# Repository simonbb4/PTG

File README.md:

# PTG
Programmable Tone Generator Senior Design Project Texas State University

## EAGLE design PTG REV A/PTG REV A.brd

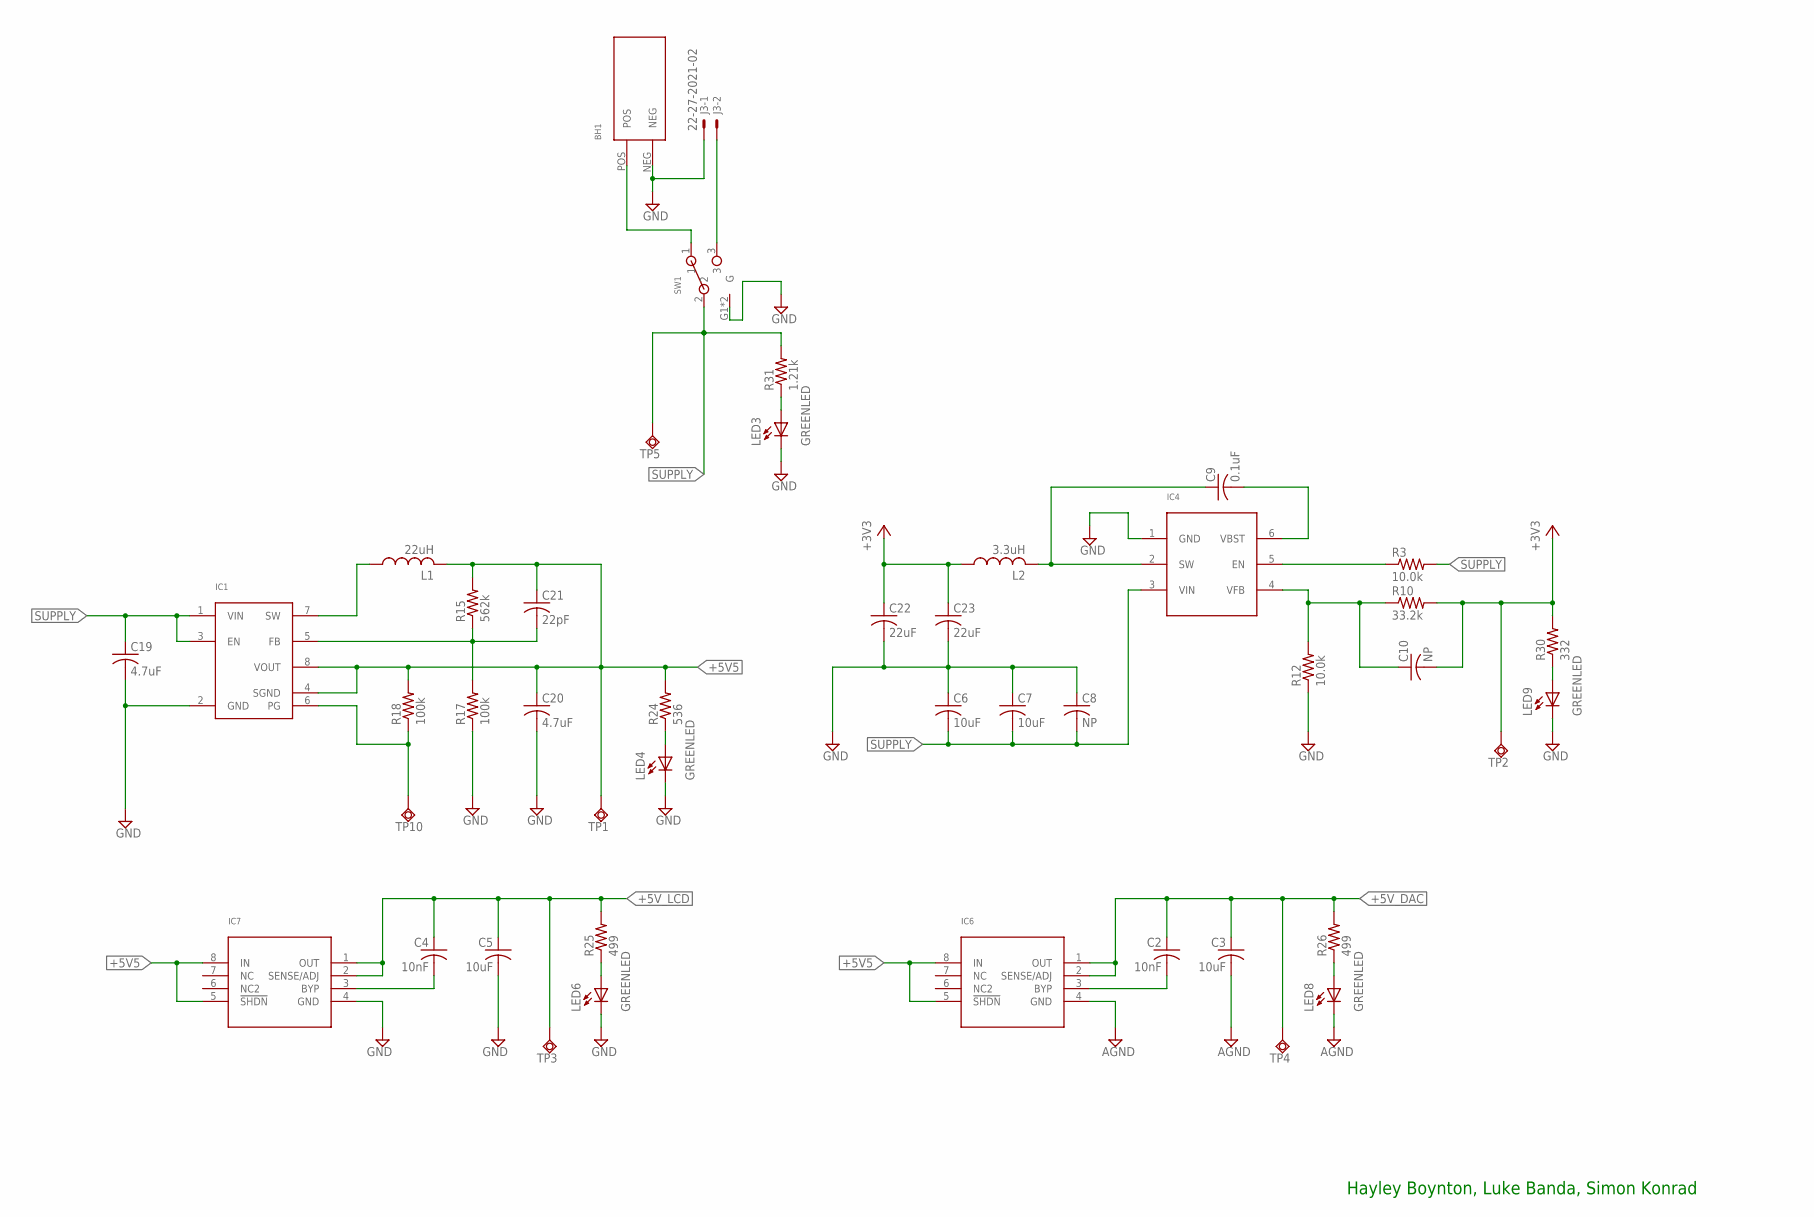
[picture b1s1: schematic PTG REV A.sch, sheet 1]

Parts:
BH1: BATTERY_HOLDER
C2, C4: 10nF; C0603K
C3, C5, C6, C7: 10uF; C0805K
C8: NP; C0805K
C9: 0.1uF; C0603K
C10: NP; C0603K
C19, C20: 4.7uF; C0805K
C21: 22pF; C0603K
C22, C23: 22uF; C0805K
IC1: TPS62120; SOT23(8)
IC4: TPS561208; SOT6
IC6, IC7: LT1762; MS8
J3: 22-27-2021-02; 6410-02
L1: 22uH; VLCF4020
L2: 3.3uH; VLCF4020
LED3, LED4, LED6, LED8, LED9: GREENLED; 0805_10MGAP
R3, R12: 10.0k; R0603
R10: 33.2k; R0603
R15: 562k; R0603
R17, R18: 100k; R0603
R24: 536; R0603
R25, R26: 499; R0603
R30: 332; R0603
R31: 1.21k; R0603
SW1: ROCKER_SWITCH
TP1, TP2, TP3, TP4, TP5, TP10: TPSQTP20SQD; TP20SQD

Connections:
+3V3: C10.2, C22.1, C23.1, L2.1, R10.2, R30.2, TP2.1, TP2.TP; also elsewhere on the board
+5V5: C20.1, C21.1, IC1.4 (SGND), IC1.8 (VOUT), IC6.5 (!SHDN), IC6.8 (IN), IC7.5 (!SHDN), IC7.8 (IN), L1.2, R15.2, R18.2, R24.2, TP1.1, TP1.TP
+5V_DAC: C2.1, C3.1, IC6.1 (OUT), IC6.2 (SENSE/ADJ), R26.2, TP4.1, TP4.TP; also elsewhere on the board
+5V_LCD: C4.1, C5.1, IC7.1 (OUT), IC7.2 (SENSE/ADJ), R25.2, TP3.1, TP3.TP; also elsewhere on the board
AGND: C3.2, IC6.4 (GND), LED8.1 (-); also elsewhere on the board
GND: BH1.NEG, C5.2, C6.1, C7.1, C8.1, C19.2, C20.2, C22.2, C23.2, IC1.2 (GND), IC4.1 (GND), IC7.4 (GND), J3.1, LED3.1 (-), LED4.1 (-), LED6.1 (-), LED9.1 (-), R12.1, R17.1, SW1.G1 (G), SW1.G2 (G); also elsewhere on the board
unnamed: C10.1, IC4.4 (VFB), R10.1, R12.2
unnamed: C9.1, IC4.2 (SW), L2.2
unnamed: C9.2, IC4.6 (VBST)
unnamed: IC4.5 (EN), R3.1
unnamed: IC1.7 (SW), L1.1
unnamed: C21.2, IC1.5 (FB), R15.1, R17.2
unnamed: C2.2, IC6.3 (BYP)
unnamed: LED3.2 (+), R31.1
unnamed: LED4.2 (+), R24.1
unnamed: C4.2, IC7.3 (BYP)
unnamed: LED6.2 (+), R25.1
unnamed: LED8.2 (+), R26.1
unnamed: LED9.2 (+), R30.1
unnamed: BH1.POS, SW1.1
unnamed: J3.2, SW1.3
PWRGOOD: IC1.6 (PG), R18.1, TP10.1, TP10.TP
SUPPLY: C6.2, C7.2, C8.2, C19.1, IC1.1 (VIN), IC1.3 (EN), IC4.3 (VIN), R3.2, R31.2, SW1.2, TP5.1, TP5.TP

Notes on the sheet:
Hayley Boynton, Luke Banda, Simon Konrad

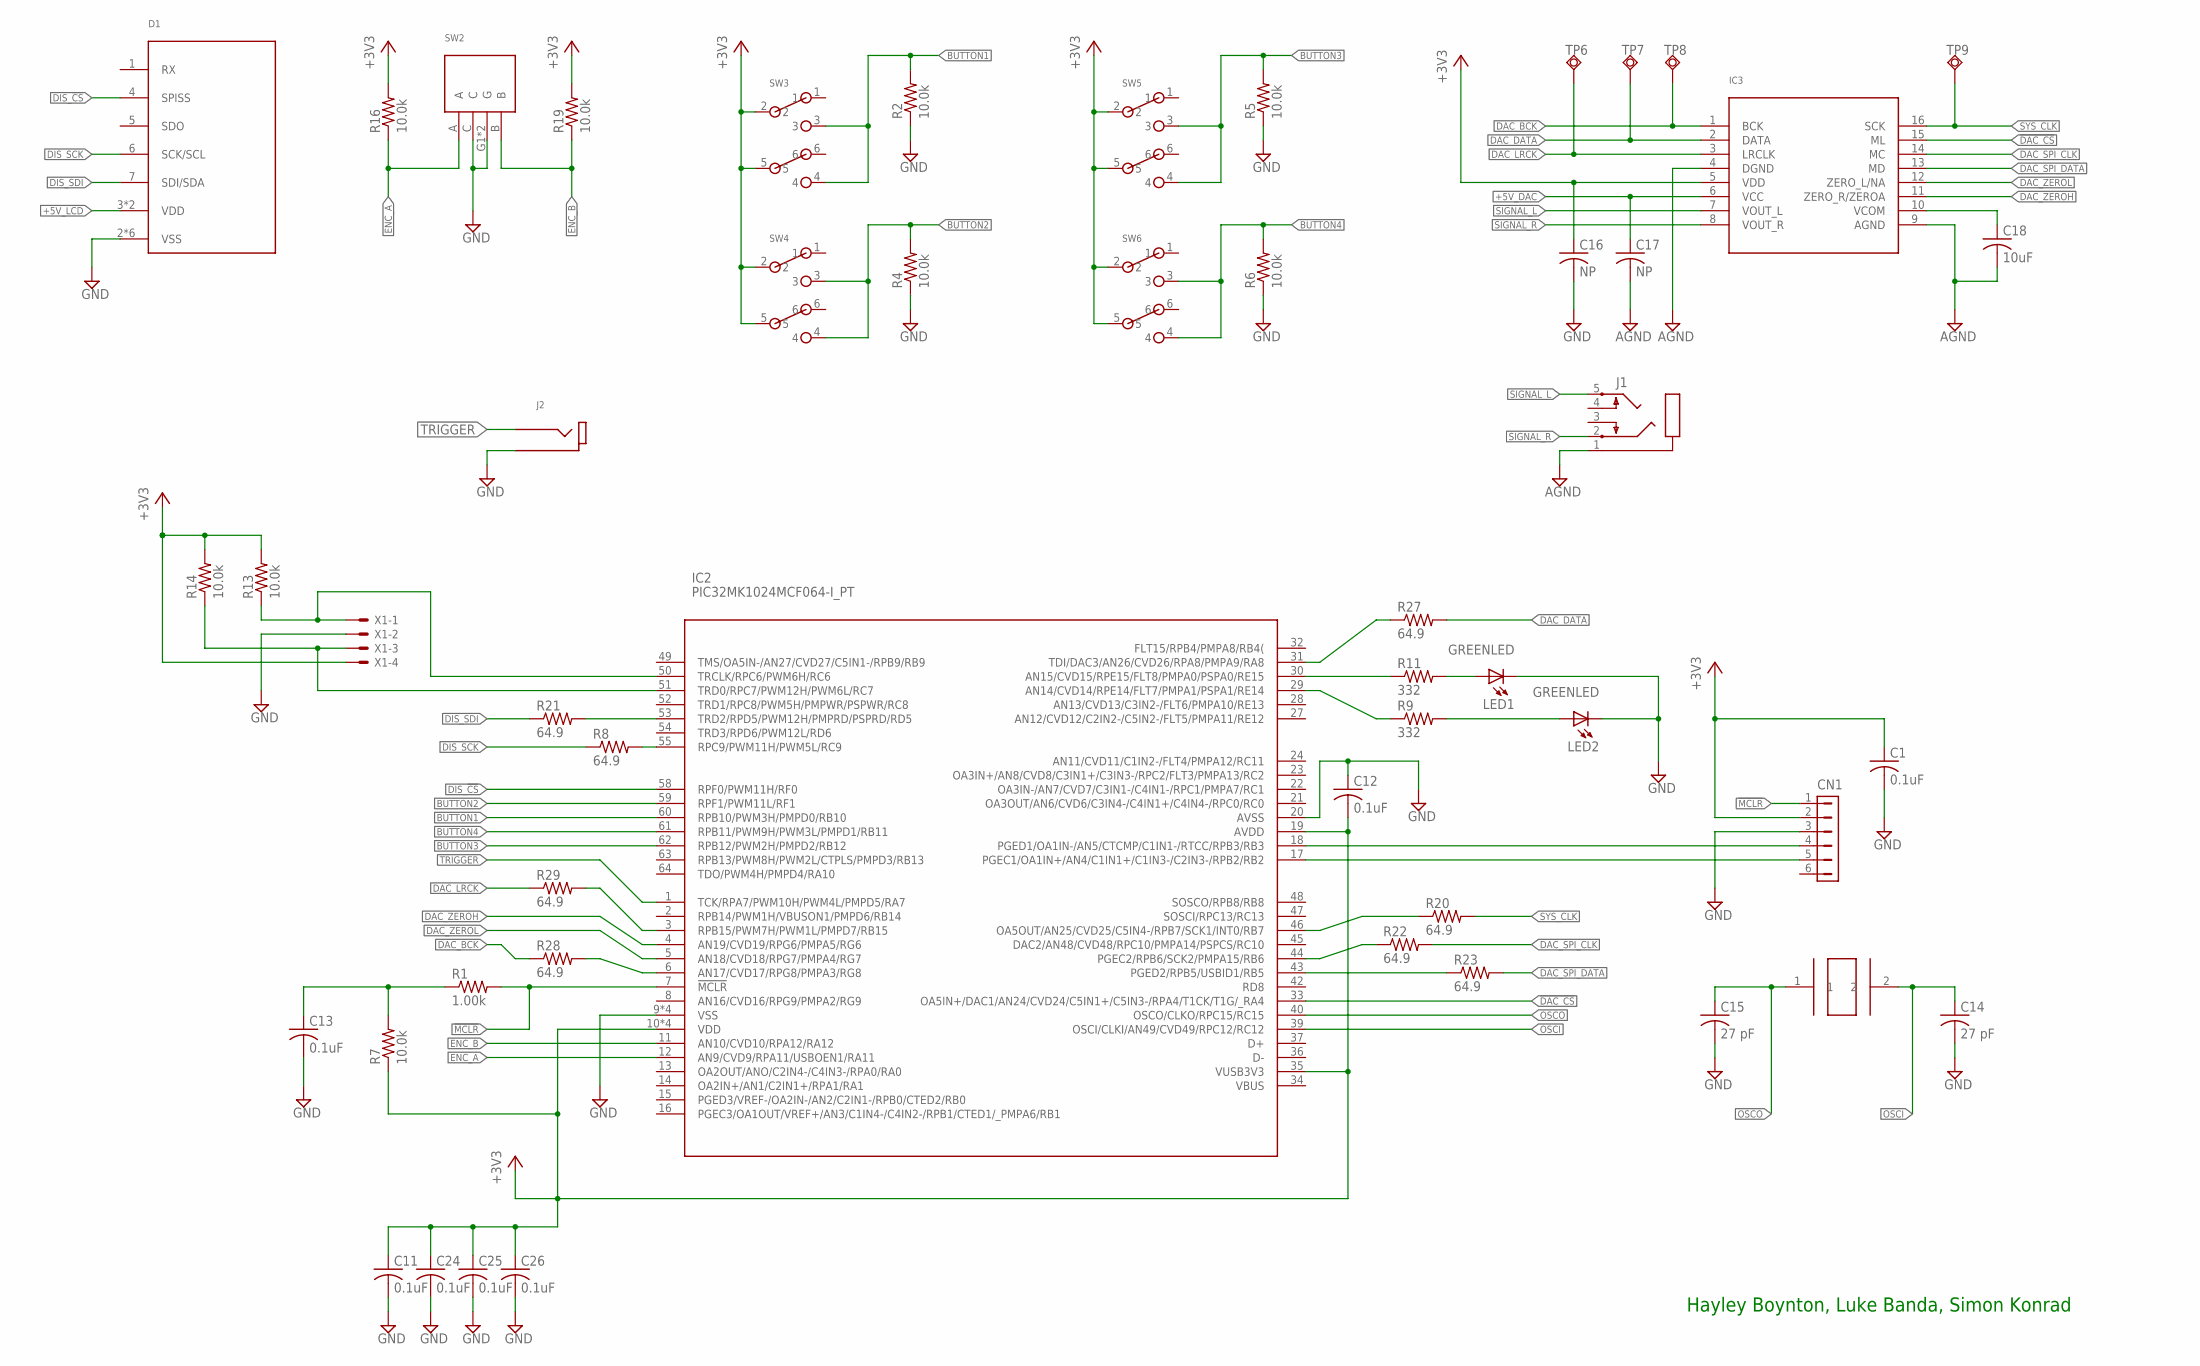
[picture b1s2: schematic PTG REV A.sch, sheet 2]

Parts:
C1, C11, C12, C13, C24, C25, C26: 0.1uF; C0603K
C14, C15: 27 pF; C0603K
C16, C17: NP; C0603K
C18: 10uF; C0805K
CN1: HDR-1X6-SIP-100; SIP-100-6V
D1: NHD-0216K3Z-GBW-V3; NHD-0216K3Z-FL-GBW-V3
IC2: PIC32MK1024MCF064-I_PT; TQFP64-10X10
IC3: PCM1748; SSOP
J1: STX31005NB
J2: RCJ-01X
LED1, LED2: GREENLED; 0805_10MGAP
R1: 1.00k; R0603
R2, R4, R5, R6, R7, R13, R14, R16, R19: 10.0k; R0603
R8, R20, R21, R22, R23, R27, R28, R29: 64.9; R0603
R9, R11: 332; R0603
SW2: ENCODER; EC12E24204A7
SW3, SW4, SW5, SW6: MHPS2273N
TP6, TP7, TP8, TP9: TPSQTP20SQD; TP20SQD
X1: 22-23-2041
Y1: EXTERNALCRYSTAL; XTAL500X320X130N

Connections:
!DAC_CS: IC2.33 (OA5IN+/DAC1/AN24/CVD24/C5IN1+/C5IN3-/RP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), IC3.15 (ML)
!MCLR: CN1.1, IC2.7 (!MCLR), R1.2
+3V3: C1.1, C11.1, C12.2, C16.1, C24.1, C25.1, C26.1, CN1.2, IC2.10 (VDD), IC2.19 (AVDD), IC2.26 (VDD), IC2.35 (VUSB3V3), IC2.38 (VDD), IC2.57 (VDD), IC3.5 (VDD), R7.1, R13.2, R14.2, R16.2, R19.2, SW3.2, SW3.5, SW4.2, SW4.5, SW5.2, SW5.5, SW6.2, SW6.5, X1.4; also elsewhere on the board
+5V_DAC: C17.1, IC3.6 (VCC); also elsewhere on the board
+5V_LCD: D1.3 (VDD), D1.9 (VDD); also elsewhere on the board
AGND: C17.2, C18.2, IC3.4 (DGND), IC3.9 (AGND), J1.1; also elsewhere on the board
BUTTON1: IC2.60 (RPB10/PWM3H/PMPD0/RB10), R2.2, SW3.3, SW3.4
BUTTON2: IC2.59 (RPF1/PWM11L/RF1), R4.2, SW4.3, SW4.4
BUTTON3: IC2.62 (RPB12/PWM2H/PMPD2/RB12), R5.2, SW5.3, SW5.4
BUTTON4: IC2.61 (RPB11/PWM9H/PWM3L/PMPD1/RB11), R6.2, SW6.3, SW6.4
DAC_BCK: IC3.1 (BCK), R28.1, TP8.1, TP8.TP
DAC_DATA: IC3.2 (DATA), R27.2, TP7.1, TP7.TP
DAC_LRCK: IC3.3 (LRCLK), R29.1, TP6.1, TP6.TP
DAC_SPI_CLK: IC3.14 (MC), R22.2
DAC_SPI_DATA: IC3.13 (MD), R23.2
DAC_ZEROH: IC2.4 (AN19/CVD19/RPG6/PMPA5/RG6), IC3.11 (ZERO_R/ZEROA)
DAC_ZEROL: IC2.5 (AN18/CVD18/RPG7/PMPA4/RG7), IC3.12 (ZERO_L/NA)
DIS_!CS: D1.4 (SPISS), IC2.58 (RPF0/PWM11H/RF0)
DIS_SCK: D1.6 (SCK/SCL), R8.1
DIS_SDI: D1.7 (SDI/SDA), R21.1
ENC_A: IC2.12 (AN9/CVD9/RPA11/USBOEN1/RA11), R16.1, SW2.A
ENC_B: IC2.11 (AN10/CVD10/RPA12/RA12), R19.1, SW2.B
GND: C1.2, C11.2, C12.1, C13.2, C14.2, C15.2, C16.2, C24.2, C25.2, C26.2, CN1.3, D1.2 (VSS), D1.8 (VSS), D1.G1 (VSS), D1.G2 (VSS), D1.G3 (VSS), D1.G4 (VSS), IC2.9 (VSS), IC2.20 (AVSS), IC2.25 (VSS), IC2.41 (VSS), IC2.56 (VSS), J2.1, J2.3 (1), J2.4 (1), LED1.1 (-), LED2.1 (-), R2.1, R4.1, R5.1, R6.1, SW2.C, SW2.G1 (G), SW2.G2 (G), X1.2; also elsewhere on the board
unnamed: IC2.31 (TDI/DAC3/AN26/CVD26/RPA8/PMPA9/RA8), R27.1
unnamed: IC2.55 (RPC9/PWM11H/PWM5L/RC9), R8.2
unnamed: IC2.53 (TRD2/RPD5/PWM12H/PMPRD/PSPRD/RD5), R21.2
unnamed: IC2.30 (AN15/CVD15/RPE15/FLT8/PMPA0/PSPA0/RE15), R11.1
unnamed: LED1.2 (+), R11.2
unnamed: IC2.46 (OA5OUT/AN25/CVD25/C5IN4-/RPB7/SCK1/INT0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), R20.1
unnamed: LED2.2 (+), R9.2
unnamed: CN1.5, IC2.17 (PGEC1/OA1IN+/AN4/C1IN1+/C1IN3-/C2IN3-/R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)
unnamed: IC2.29 (AN14/CVD14/RPE14/FLT7/PMPA1/PSPA1/RE14), R9.1
unnamed: C13.1, R1.1, R7.2
unnamed: C18.1, IC3.10 (VCOM)
unnamed: IC2.3 (RPB15/PWM7H/PWM1L/PMPD7/RB15), R29.2
unnamed: IC2.44 (PGEC2/RPB6/SCK2/PMPA15/RB6), R22.1
unnamed: CN1.4, IC2.18 (PGED1/OA1IN-/AN5/CTCMP/C1IN1-/RTCC/RPB3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)
unnamed: IC2.43 (PGED2/RPB5/USBID1/RB5), R23.1
unnamed: IC2.6 (AN17/CVD17/RPG8/PMPA3/RG8), R28.2
OSCI: C14.1, IC2.39 (OSCI/CLKI/AN49/CVD49/RPC12/RC12), Y1.2
OSCO: C15.1, IC2.40 (OSCO/CLKO/RPC15/RC15), Y1.1
SIGNAL_L: IC3.7 (VOUT_L), J1.5
SIGNAL_R: IC3.8 (VOUT_R), J1.2
SYS_CLK: IC3.16 (SCK), R20.2, TP9.1, TP9.TP
TRIGGER: IC2.1 (TCK/RPA7/PWM10H/PWM4L/PMPD5/RA7), J2.2
UART-RX: IC2.50 (TRCLK/RPC6/PWM6H/RC6), R13.1, X1.1
UART-TX: IC2.51 (TRD0/RPC7/PWM12H/PWM6L/RC7), R14.1, X1.3

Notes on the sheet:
Hayley Boynton, Luke Banda, Simon Konrad

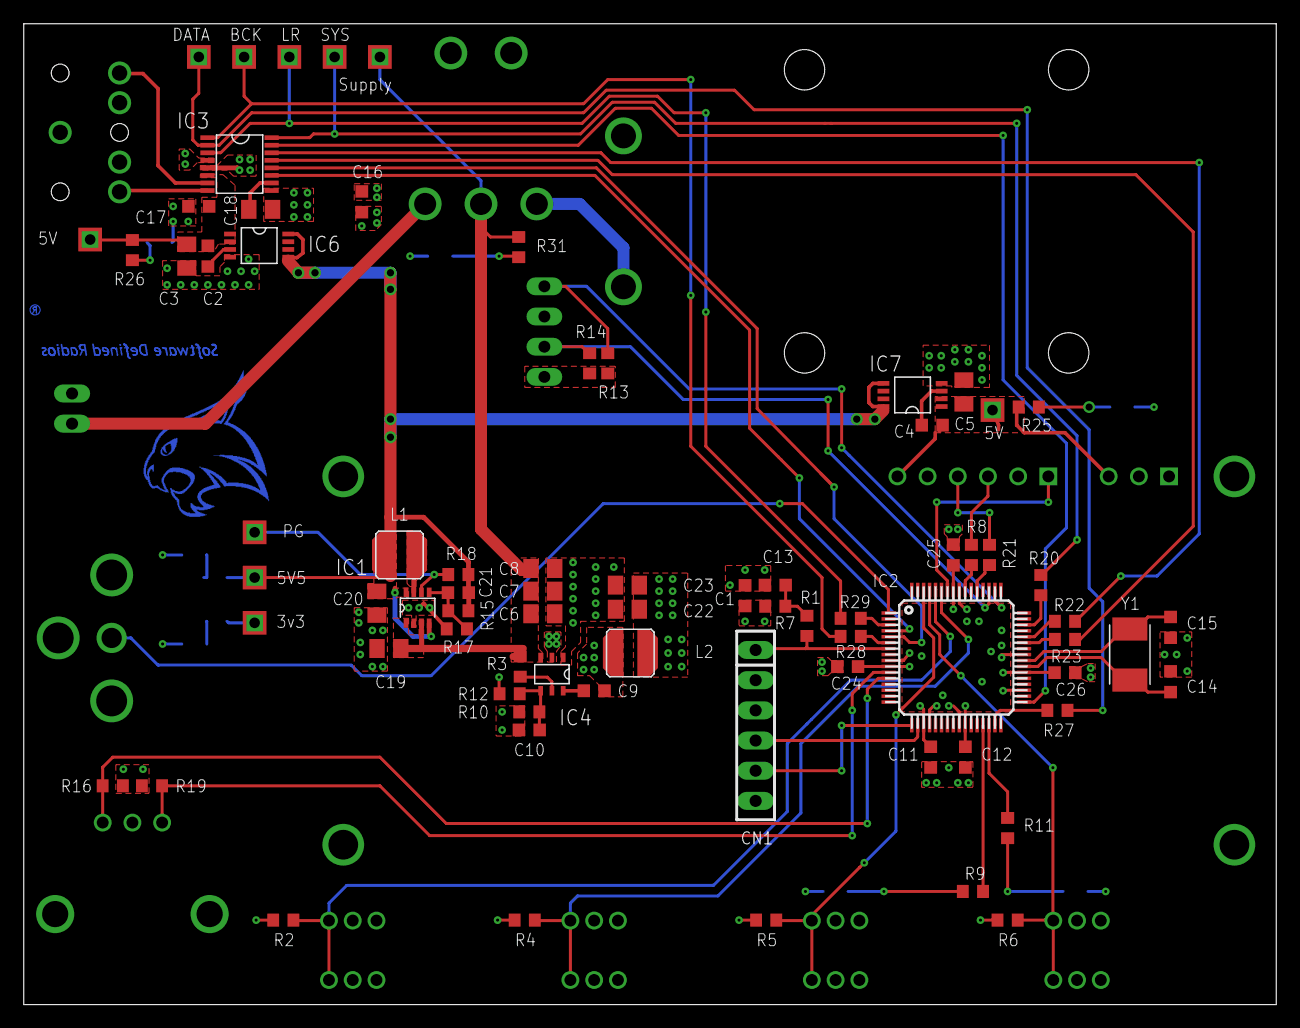
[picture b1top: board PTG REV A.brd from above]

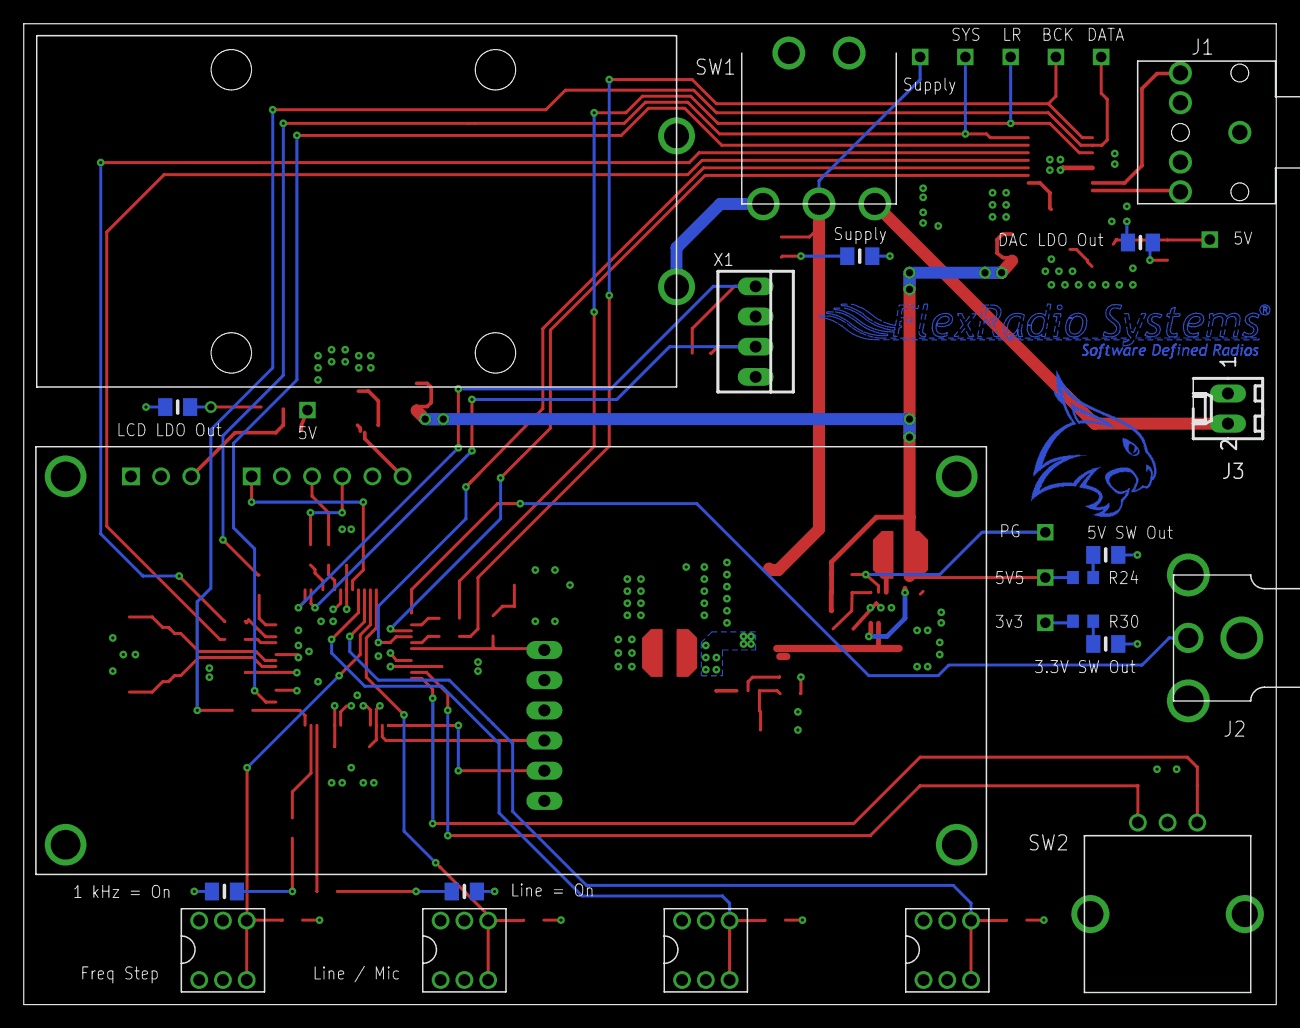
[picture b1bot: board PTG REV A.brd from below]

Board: 4 copper layers, 105.4 x 82.5 mm, 96 parts (21 on the bottom side), 65 nets.

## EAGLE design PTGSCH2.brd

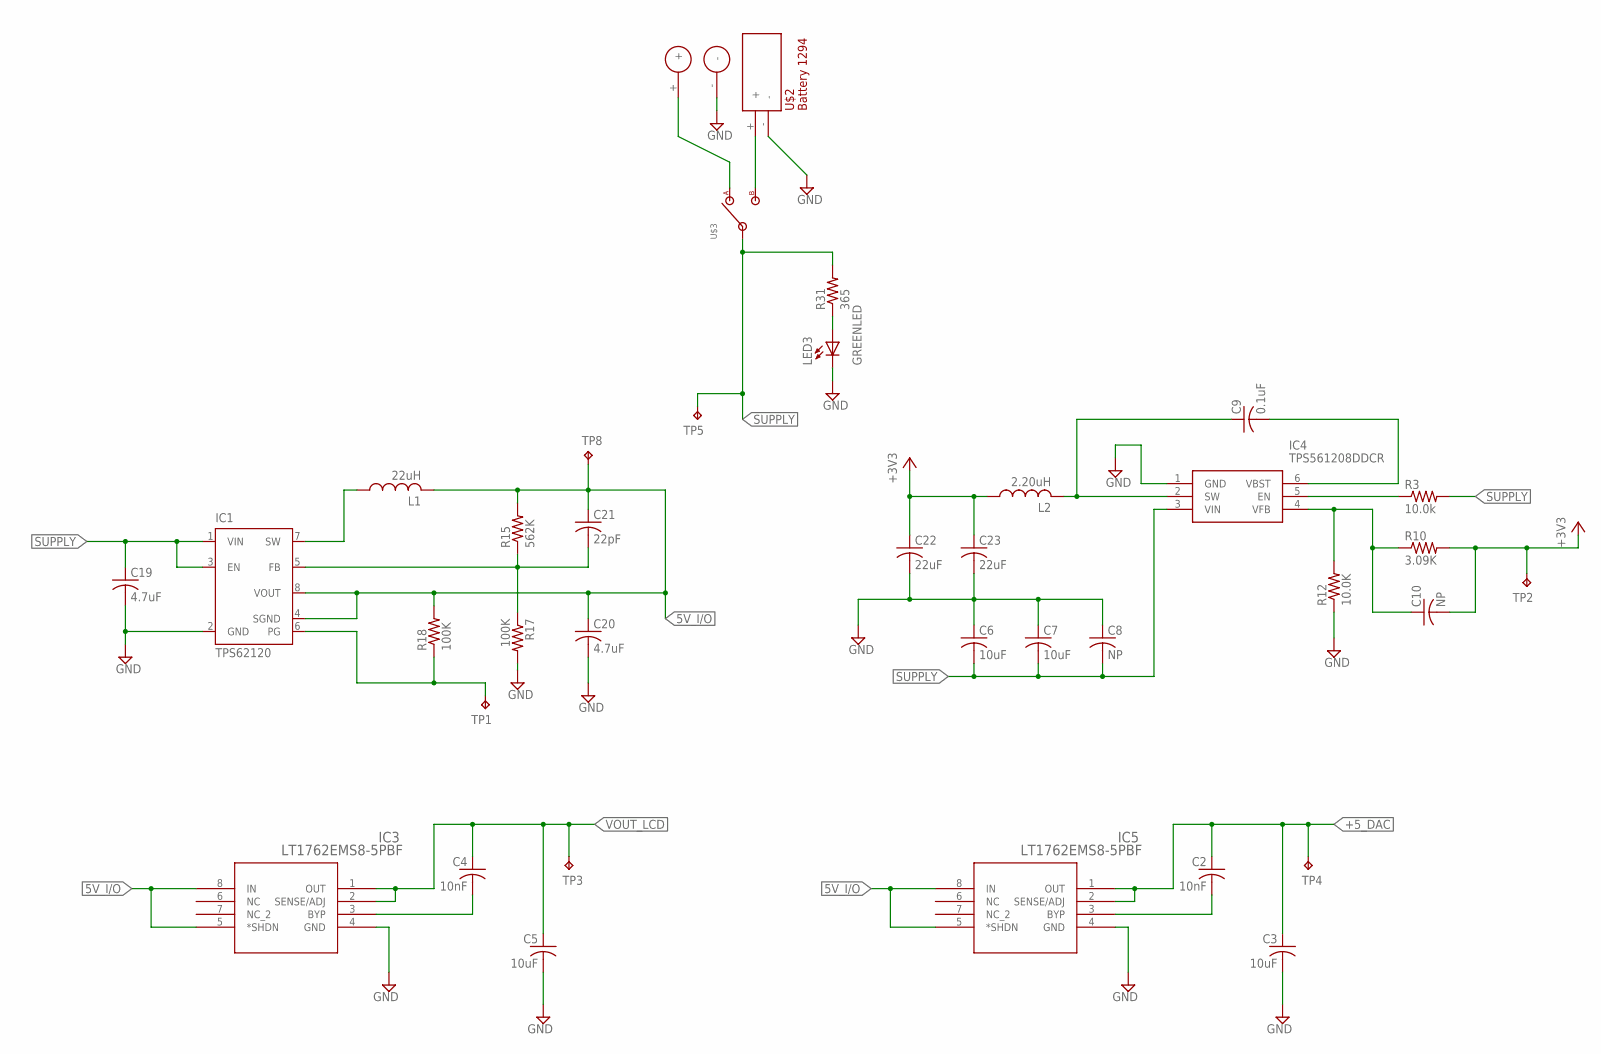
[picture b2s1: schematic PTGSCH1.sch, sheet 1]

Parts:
C2, C4: 10nF; C0603
C3, C5, C6, C7: 10uF; C0805
C8, C10: NP; C0805
C9: 0.1uF; C0805
C19, C20: 4.7uF; C0603
C21: 22pF; C0603
C22, C23: 22uF; C0603
IC1: TPS62120; DCN-R-PDSO-G8
IC3, IC5: LT1762EMS8-5PBF; MSOP-8_MS
IC4: TPS561208DDCR; SOT95P280X110-6N
L1: 22uH; C0603K
L2: 2.20uH; C0603K
LED3: GREENLED; 0805_10MGAP
R3: 10.0k; R0603
R10: 3.09K; R0603
R12: 10.0K; R0603
R15: 562K; R0603
R17, R18: 100K; R0603
R31: 365; R0603
TP1, TP2, TP3, TP4, TP5, TP8: TPTP20SQ; TP20SQ
U$2: BATTERY_HOLDER; HOLDER
U$3: POWERSWITCH; ROCKERVIAS
U$4: POWRPINS; VOLTAGEPINS

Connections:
5V_I/O: C20.1, C21.1, IC1.4 (SGND), IC1.8 (VOUT), IC3.5 (*SHDN), IC3.8 (IN), IC5.5 (*SHDN), IC5.8 (IN), L1.2, R15.2, R18.2, TP8.TP
+3V3: C10.2, C22.1, C23.1, L2.1, R10.2, TP2.TP; also elsewhere on the board
+5_DAC: C2.1, C3.1, IC5.1 (OUT), IC5.2 (SENSE/ADJ), TP4.TP; also elsewhere on the board
ADD_TEST_PAD: IC1.6 (PG), R18.1, TP1.TP
GND: C3.2, C5.2, C6.1, C7.1, C8.1, C19.2, C20.2, C22.2, C23.2, IC1.2 (GND), IC3.4 (GND), IC4.1 (GND), IC5.4 (GND), LED3.1 (-), R12.1, R17.2, U$2.-, U$4.-; also elsewhere on the board
unnamed: U$2.+, U$3.3
unnamed: C10.1, IC4.4 (VFB), R10.1, R12.2
unnamed: C9.1, IC4.2 (SW), L2.2
unnamed: C9.2, IC4.6 (VBST)
unnamed: IC4.5 (EN), R3.1
unnamed: IC1.7 (SW), L1.1
unnamed: C21.2, IC1.5 (FB), R15.1, R17.1
unnamed: C2.2, IC5.3 (BYP)
unnamed: LED3.2 (+), R31.1
unnamed: C4.2, IC3.3 (BYP)
PWR_PINS: U$3.1, U$4.+
SUPPLY: C6.2, C7.2, C8.2, C19.1, IC1.1 (VIN), IC1.3 (EN), IC4.3 (VIN), R3.2, R31.2, TP5.TP, U$3.2
VOUT_LCD: C4.1, C5.1, IC3.1 (OUT), IC3.2 (SENSE/ADJ), TP3.TP; also elsewhere on the board

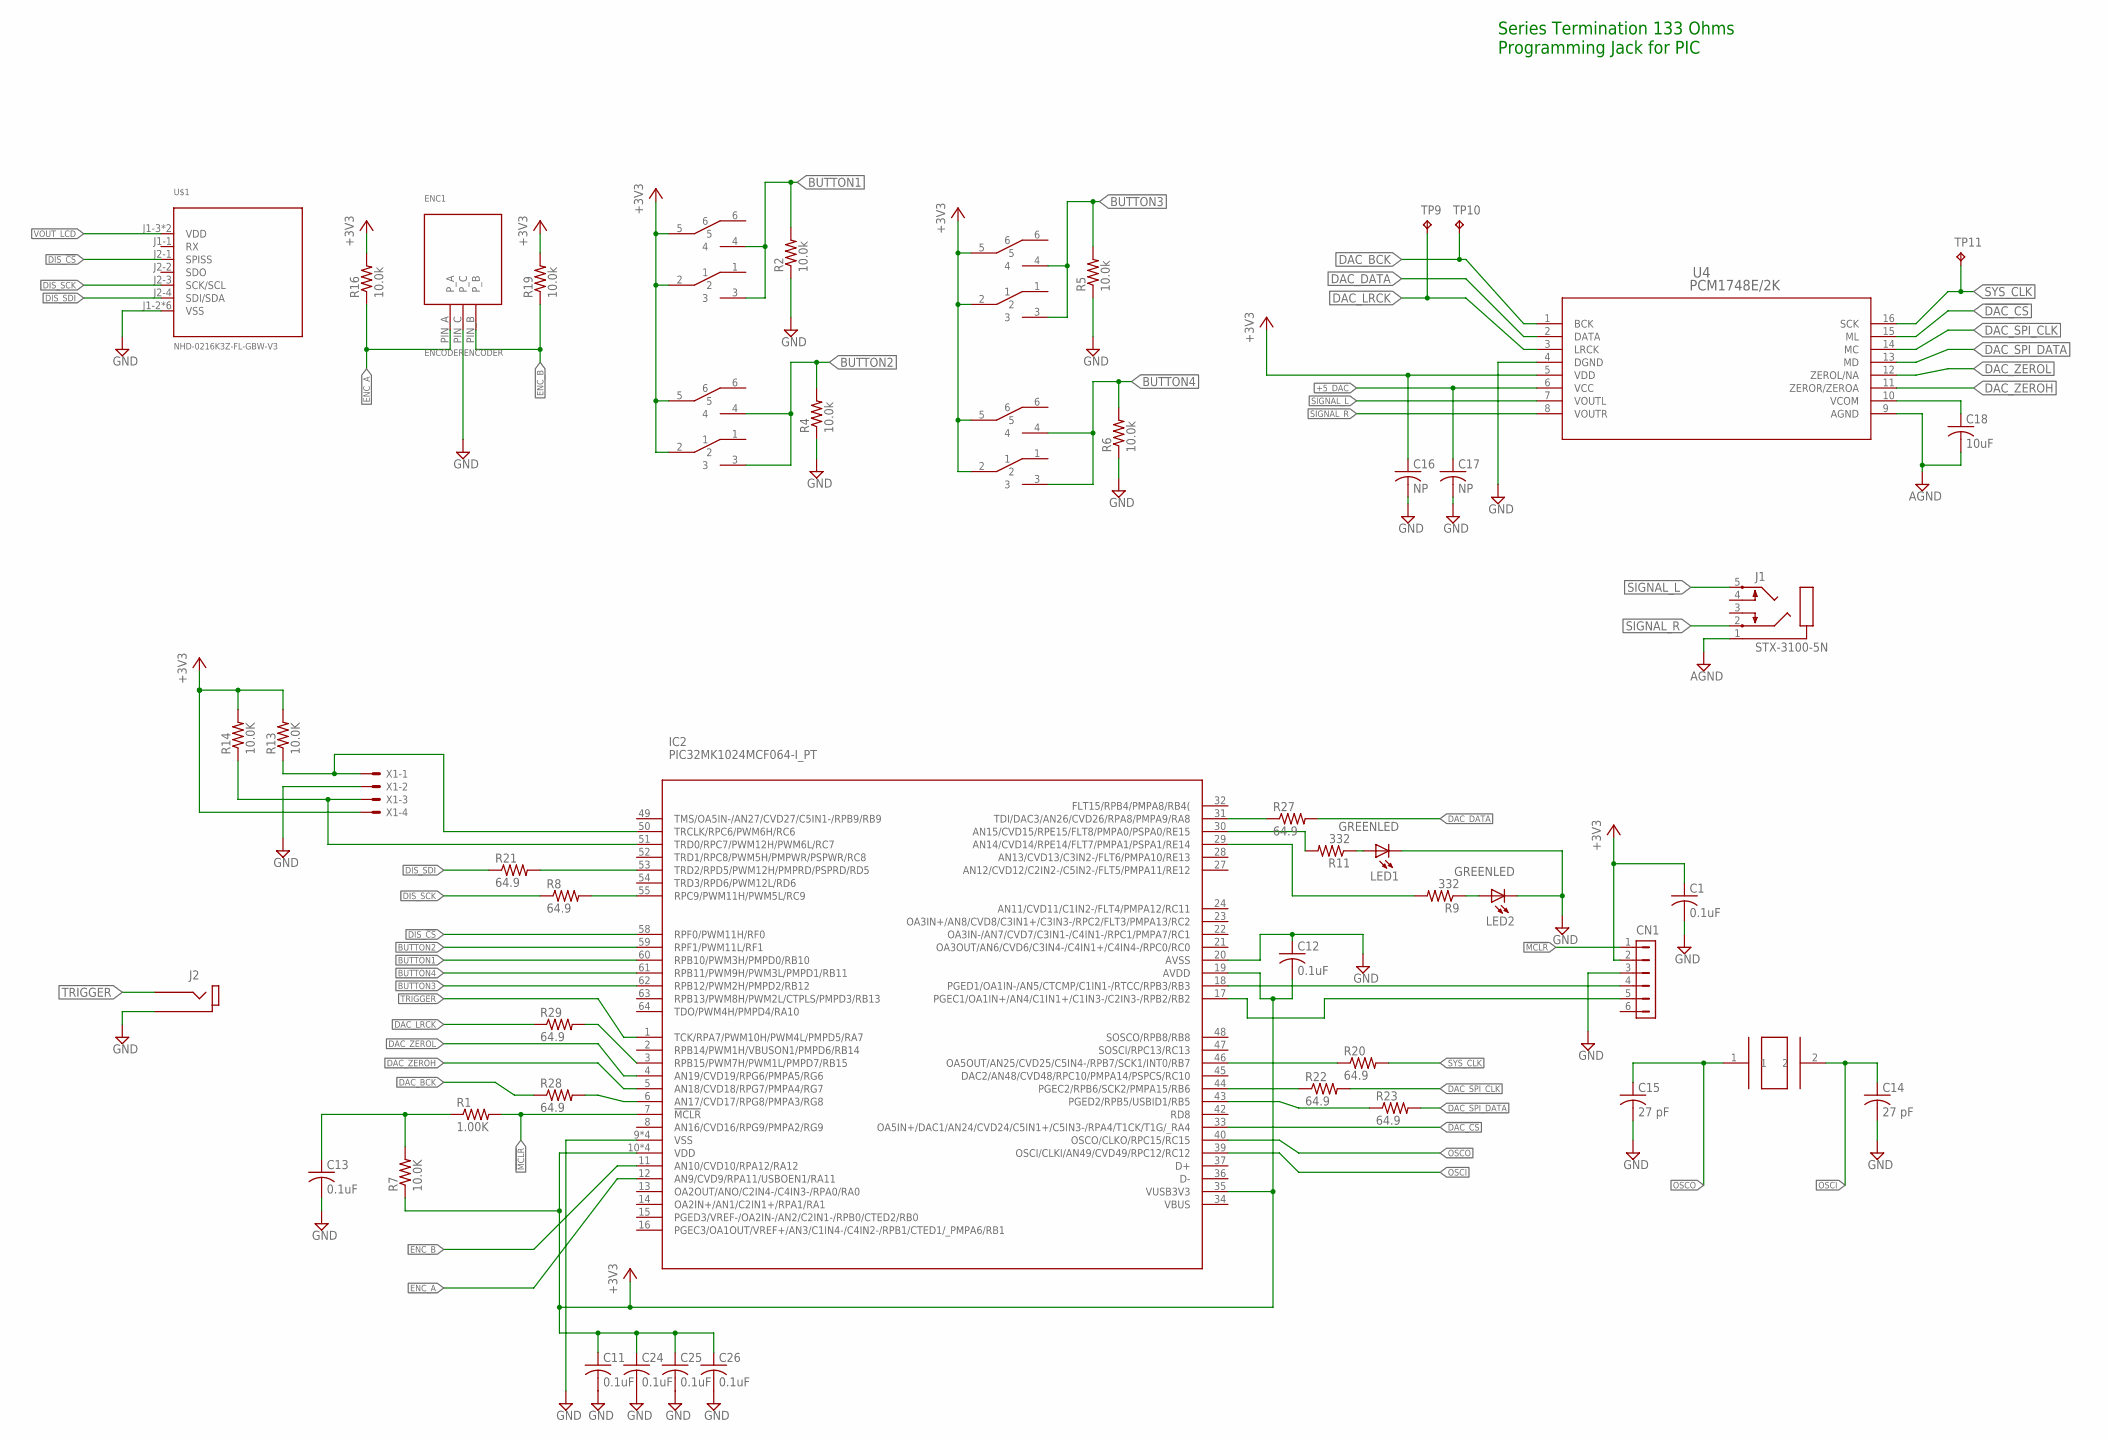
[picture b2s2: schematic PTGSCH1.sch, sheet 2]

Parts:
BUTTON1, BUTTON2, BUTTON3, BUTTON4: BUTTON-DPDT-7MM
C1, C11, C12, C13, C24, C25, C26: 0.1uF; C0805
C14, C15: 27 pF; C0603
C16, C17: NP; C0805
C18: 10uF; C0805
CN1: HDR-1X6-SIP-100; SIP-100-6V
ENC1: ENCODERENCODER; ENCODER
IC2: PIC32MK1024MCF064-I_PT; TQFP64-10X10
J1: STX-3100-5N
J2: RCJ-01X_PHONO_SINGLE; RCA_RA_PCB_SINGLE
LED1, LED2: GREENLED; 0805_10MGAP
R1: 1.00K; R0603
R2, R4, R5, R6, R16, R19: 10.0k; R0603
R7, R13, R14: 10.0K; R0603
R8, R20, R21, R22, R23, R27, R28, R29: 64.9; R0603
R9, R11: 332; R0603
TP9, TP10, TP11: TPTP20SQ; TP20SQ
U4: PCM1748E/2K; DBQ16
U$1: NHD-0216K3Z-FL-GBW-V3
U$8: EXTERNALCRYSTAL; XTAL500X320X130N
X1: 22-23-2041

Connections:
!DAC_CS: IC2.33 (OA5IN+/DAC1/AN24/CVD24/C5IN1+/C5IN3-/RP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), U4.15 (ML)
!MCLR: CN1.1, IC2.7 (!MCLR), R1.2
+3V3: BUTTON1.2, BUTTON1.5, BUTTON2.2, BUTTON2.5, BUTTON3.2, BUTTON3.5, BUTTON4.2, BUTTON4.5, C1.1, C11.1, C12.2, C16.1, C24.1, C25.1, C26.1, CN1.2, IC2.10 (VDD), IC2.19 (AVDD), IC2.26 (VDD), IC2.35 (VUSB3V3), IC2.38 (VDD), IC2.57 (VDD), R7.1, R13.2, R14.2, R16.2, R19.2, U4.5 (VDD), X1.4; also elsewhere on the board
+5_DAC: C17.1, U4.6 (VCC); also elsewhere on the board
AGND: C18.2, J1.1, U4.9 (AGND)
BUTTON1: BUTTON1.3, BUTTON1.4, IC2.60 (RPB10/PWM3H/PMPD0/RB10), R2.2
BUTTON2: BUTTON2.3, BUTTON2.4, IC2.59 (RPF1/PWM11L/RF1), R4.2
BUTTON3: BUTTON3.3, BUTTON3.4, IC2.62 (RPB12/PWM2H/PMPD2/RB12), R5.2
BUTTON4: BUTTON4.3, BUTTON4.4, IC2.61 (RPB11/PWM9H/PWM3L/PMPD1/RB11), R6.2
DAC_BCK: R28.1, TP10.TP, U4.1 (BCK)
DAC_DATA: R27.2, U4.2 (DATA)
DAC_LRCK: R29.1, TP9.TP, U4.3 (LRCK)
DAC_SPI_CLK: R22.2, U4.14 (MC)
DAC_SPI_DATA: R23.2, U4.13 (MD)
DAC_ZEROH: IC2.5 (AN18/CVD18/RPG7/PMPA4/RG7), U4.11 (ZEROR/ZEROA)
DAC_ZEROL: IC2.4 (AN19/CVD19/RPG6/PMPA5/RG6), U4.12 (ZEROL/NA)
DIS_!CS: IC2.58 (RPF0/PWM11H/RF0), U$1.J2-1 (SPISS)
DIS_SCK: R8.1, U$1.J2-3 (SCK/SCL)
DIS_SDI: R21.1, U$1.J2-4 (SDI/SDA)
ENC_A: ENC1.PIN_A (P_A), IC2.12 (AN9/CVD9/RPA11/USBOEN1/RA11), R16.1
ENC_B: ENC1.PIN_B (P_B), IC2.11 (AN10/CVD10/RPA12/RA12), R19.1
GND: C1.2, C11.2, C12.1, C13.2, C14.2, C15.2, C16.2, C17.2, C24.2, C25.2, C26.2, CN1.3, ENC1.PIN_C (P_C), IC2.9 (VSS), IC2.20 (AVSS), IC2.25 (VSS), IC2.41 (VSS), IC2.56 (VSS), J2.1 (SH), J2.3 (GND), J2.4 (GND), LED1.1 (-), LED2.1 (-), R2.1, R4.1, R5.1, R6.1, U4.4 (DGND), U$1.J1-2 (VSS), U$1.J2-5 (VSS), U$1.M1 (VSS), U$1.M2 (VSS), U$1.M3 (VSS), U$1.M4 (VSS), X1.2; also elsewhere on the board
unnamed: IC2.55 (RPC9/PWM11H/PWM5L/RC9), R8.2
unnamed: IC2.53 (TRD2/RPD5/PWM12H/PMPRD/PSPRD/RD5), R21.2
unnamed: LED2.2 (+), R9.1
unnamed: LED1.2 (+), R11.1
unnamed: IC2.46 (OA5OUT/AN25/CVD25/C5IN4-/RPB7/SCK1/INT0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), R20.1
unnamed: IC2.30 (AN15/CVD15/RPE15/FLT8/PMPA0/PSPA0/RE15), R11.2
unnamed: CN1.5, IC2.17 (PGEC1/OA1IN+/AN4/C1IN1+/C1IN3-/C2IN3-/R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)
unnamed: IC2.29 (AN14/CVD14/RPE14/FLT7/PMPA1/PSPA1/RE14), R9.2
unnamed: C13.1, R1.1, R7.2
unnamed: C18.1, U4.10 (VCOM)
unnamed: IC2.3 (RPB15/PWM7H/PWM1L/PMPD7/RB15), R29.2
unnamed: IC2.44 (PGEC2/RPB6/SCK2/PMPA15/RB6), R22.1
unnamed: CN1.4, IC2.18 (PGED1/OA1IN-/AN5/CTCMP/C1IN1-/RTCC/RPB3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)
unnamed: IC2.43 (PGED2/RPB5/USBID1/RB5), R23.1
unnamed: IC2.31 (TDI/DAC3/AN26/CVD26/RPA8/PMPA9/RA8), R27.1
unnamed: IC2.6 (AN17/CVD17/RPG8/PMPA3/RG8), R28.2
OSCI: C14.1, IC2.39 (OSCI/CLKI/AN49/CVD49/RPC12/RC12), U$8.2
OSCO: C15.1, IC2.40 (OSCO/CLKO/RPC15/RC15), U$8.1
SIGNAL_L: J1.5, U4.7 (VOUTL)
SIGNAL_R: J1.2, U4.8 (VOUTR)
SYS_CLK: R20.2, TP11.TP, U4.16 (SCK)
TRIGGER: IC2.1 (TCK/RPA7/PWM10H/PWM4L/PMPD5/RA7), J2.2 (PIN)
UART-RX: IC2.50 (TRCLK/RPC6/PWM6H/RC6), R13.1, X1.1
UART-TX: IC2.51 (TRD0/RPC7/PWM12H/PWM6L/RC7), R14.1, X1.3
VOUT_LCD: U$1.J1-3 (VDD), U$1.J2-6 (VDD); also elsewhere on the board

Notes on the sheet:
Series Termination 133 Ohms
Programming Jack for PIC

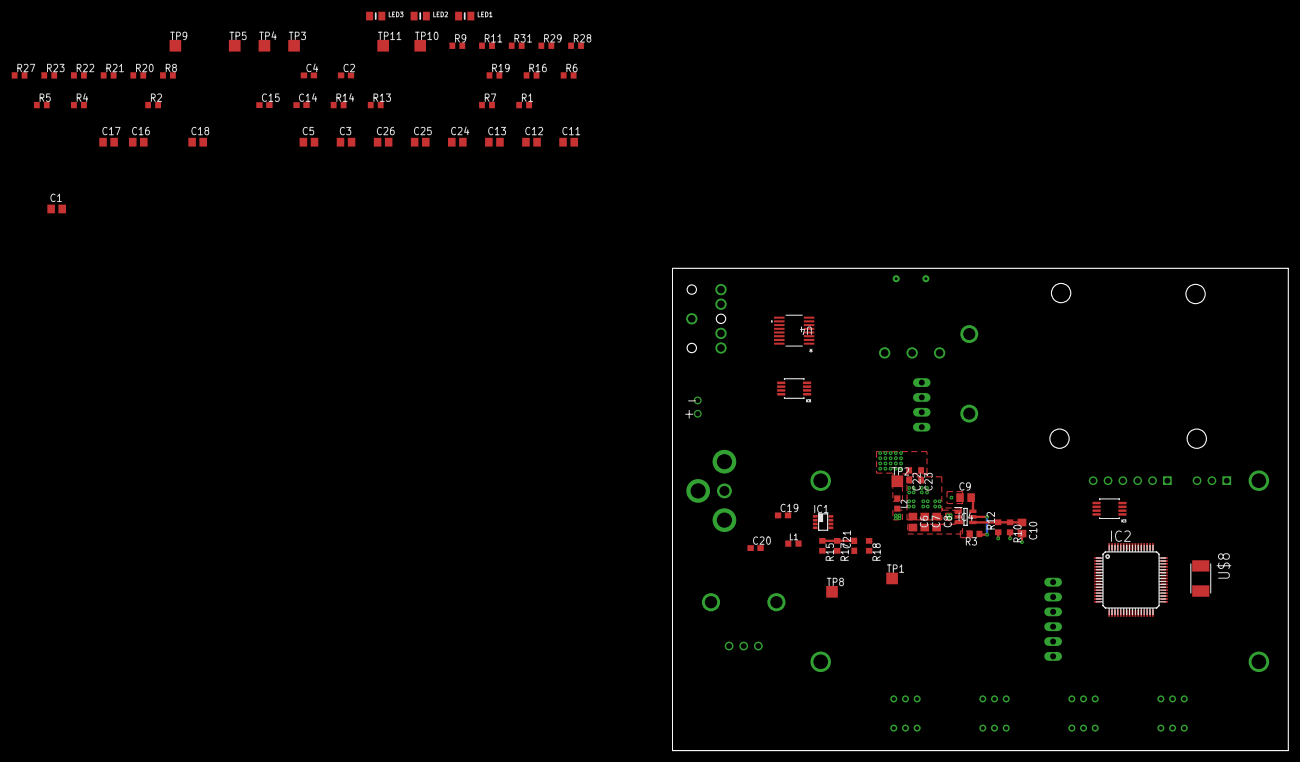
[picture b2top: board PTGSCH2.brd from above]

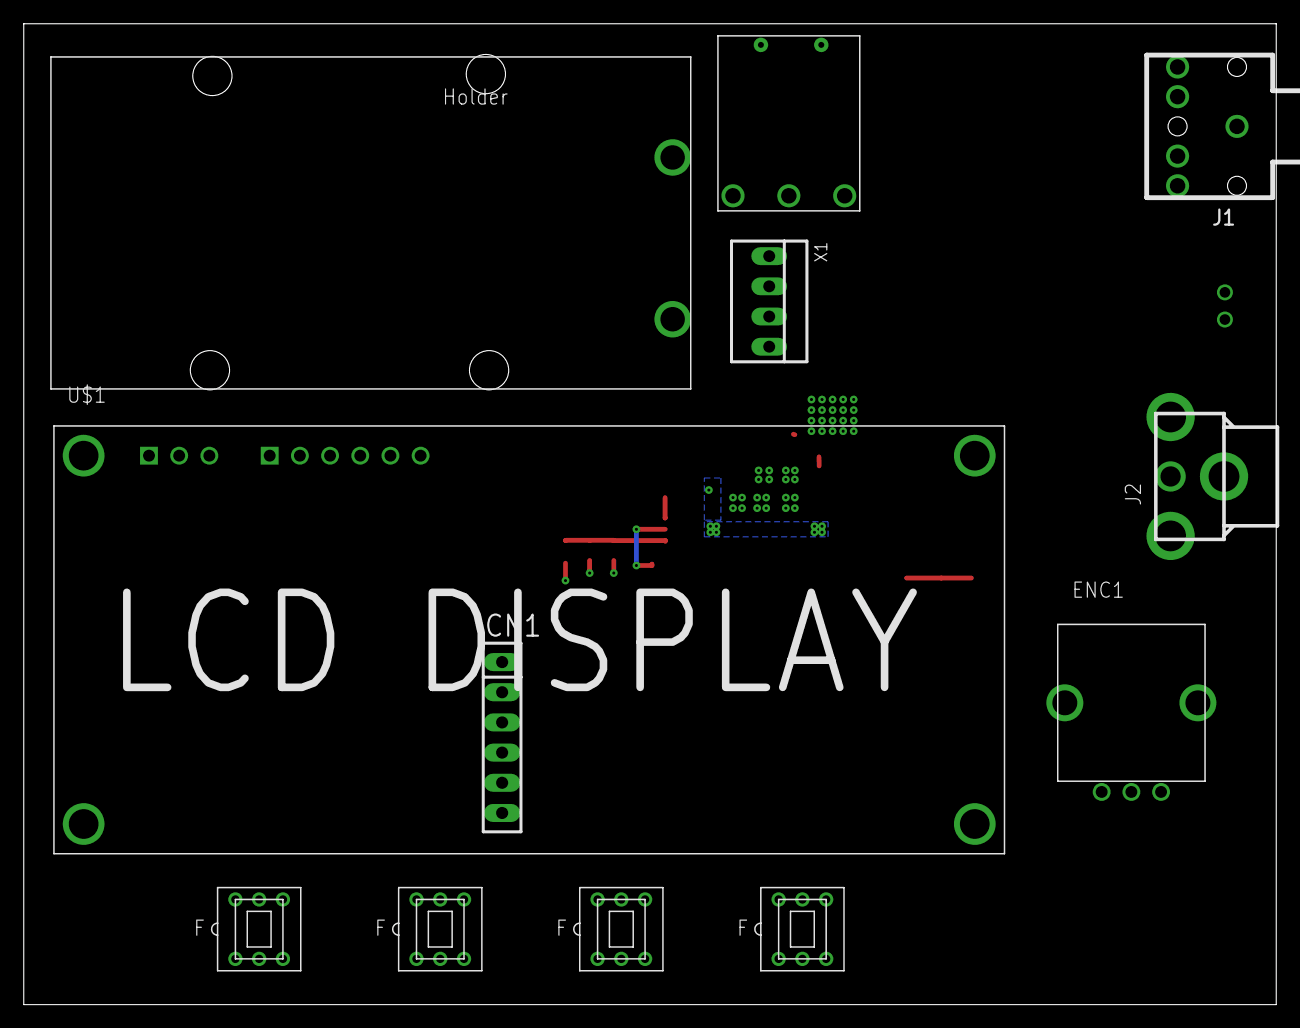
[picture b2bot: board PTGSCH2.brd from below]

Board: 4 copper layers, 105.4 x 82.5 mm, 86 parts (12 on the bottom side), 60 nets.

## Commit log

2018-05-05 Add files via upload
    SCH1 is the associated schematic.
    SCH2 is the original board design.
    SCH3 is the current board design.
2018-05-05 removing the files with the old names
2018-05-05 rename files; add .gitignore; layout for 5V switcher
2018-05-05 Add project personnel to schematic
2018-05-06 Minor changes to schematic, added LDO traces, added DAC traces, added power traces
2018-05-06 re-routed DAC data traces, added traces to all components, just connecting data traces left
2018-05-07 finished all traces except 2 I have questions on
2018-05-08 minor fixes, switched DAC_ZEROL / DAC ZEROH pins, need new test pad package
2018-05-09 changes from meeting, added logos, changed test points, changed ground plane
2018-05-09 minor changes, added power inductor, but bad library
2018-05-09 arracnged silk screen layer
2018-05-09 added libraries
2018-09-07 Fixed library symbols for chassis grounds, renamed voltage nodes, switched pins on molex power conn, updated power inductors, updated through hole RCA port
2018-09-07 correct file upload
2018-09-08 fixed 10uF cap on IC6
2018-09-08 Adding CAM job and generated gerbers for Rev A
2018-10-14 Create Code

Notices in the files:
parts and their libraries:
con-hdrs40: Copyright (C) 2004, Bob Starr (bobstarr@mindspring.com)
